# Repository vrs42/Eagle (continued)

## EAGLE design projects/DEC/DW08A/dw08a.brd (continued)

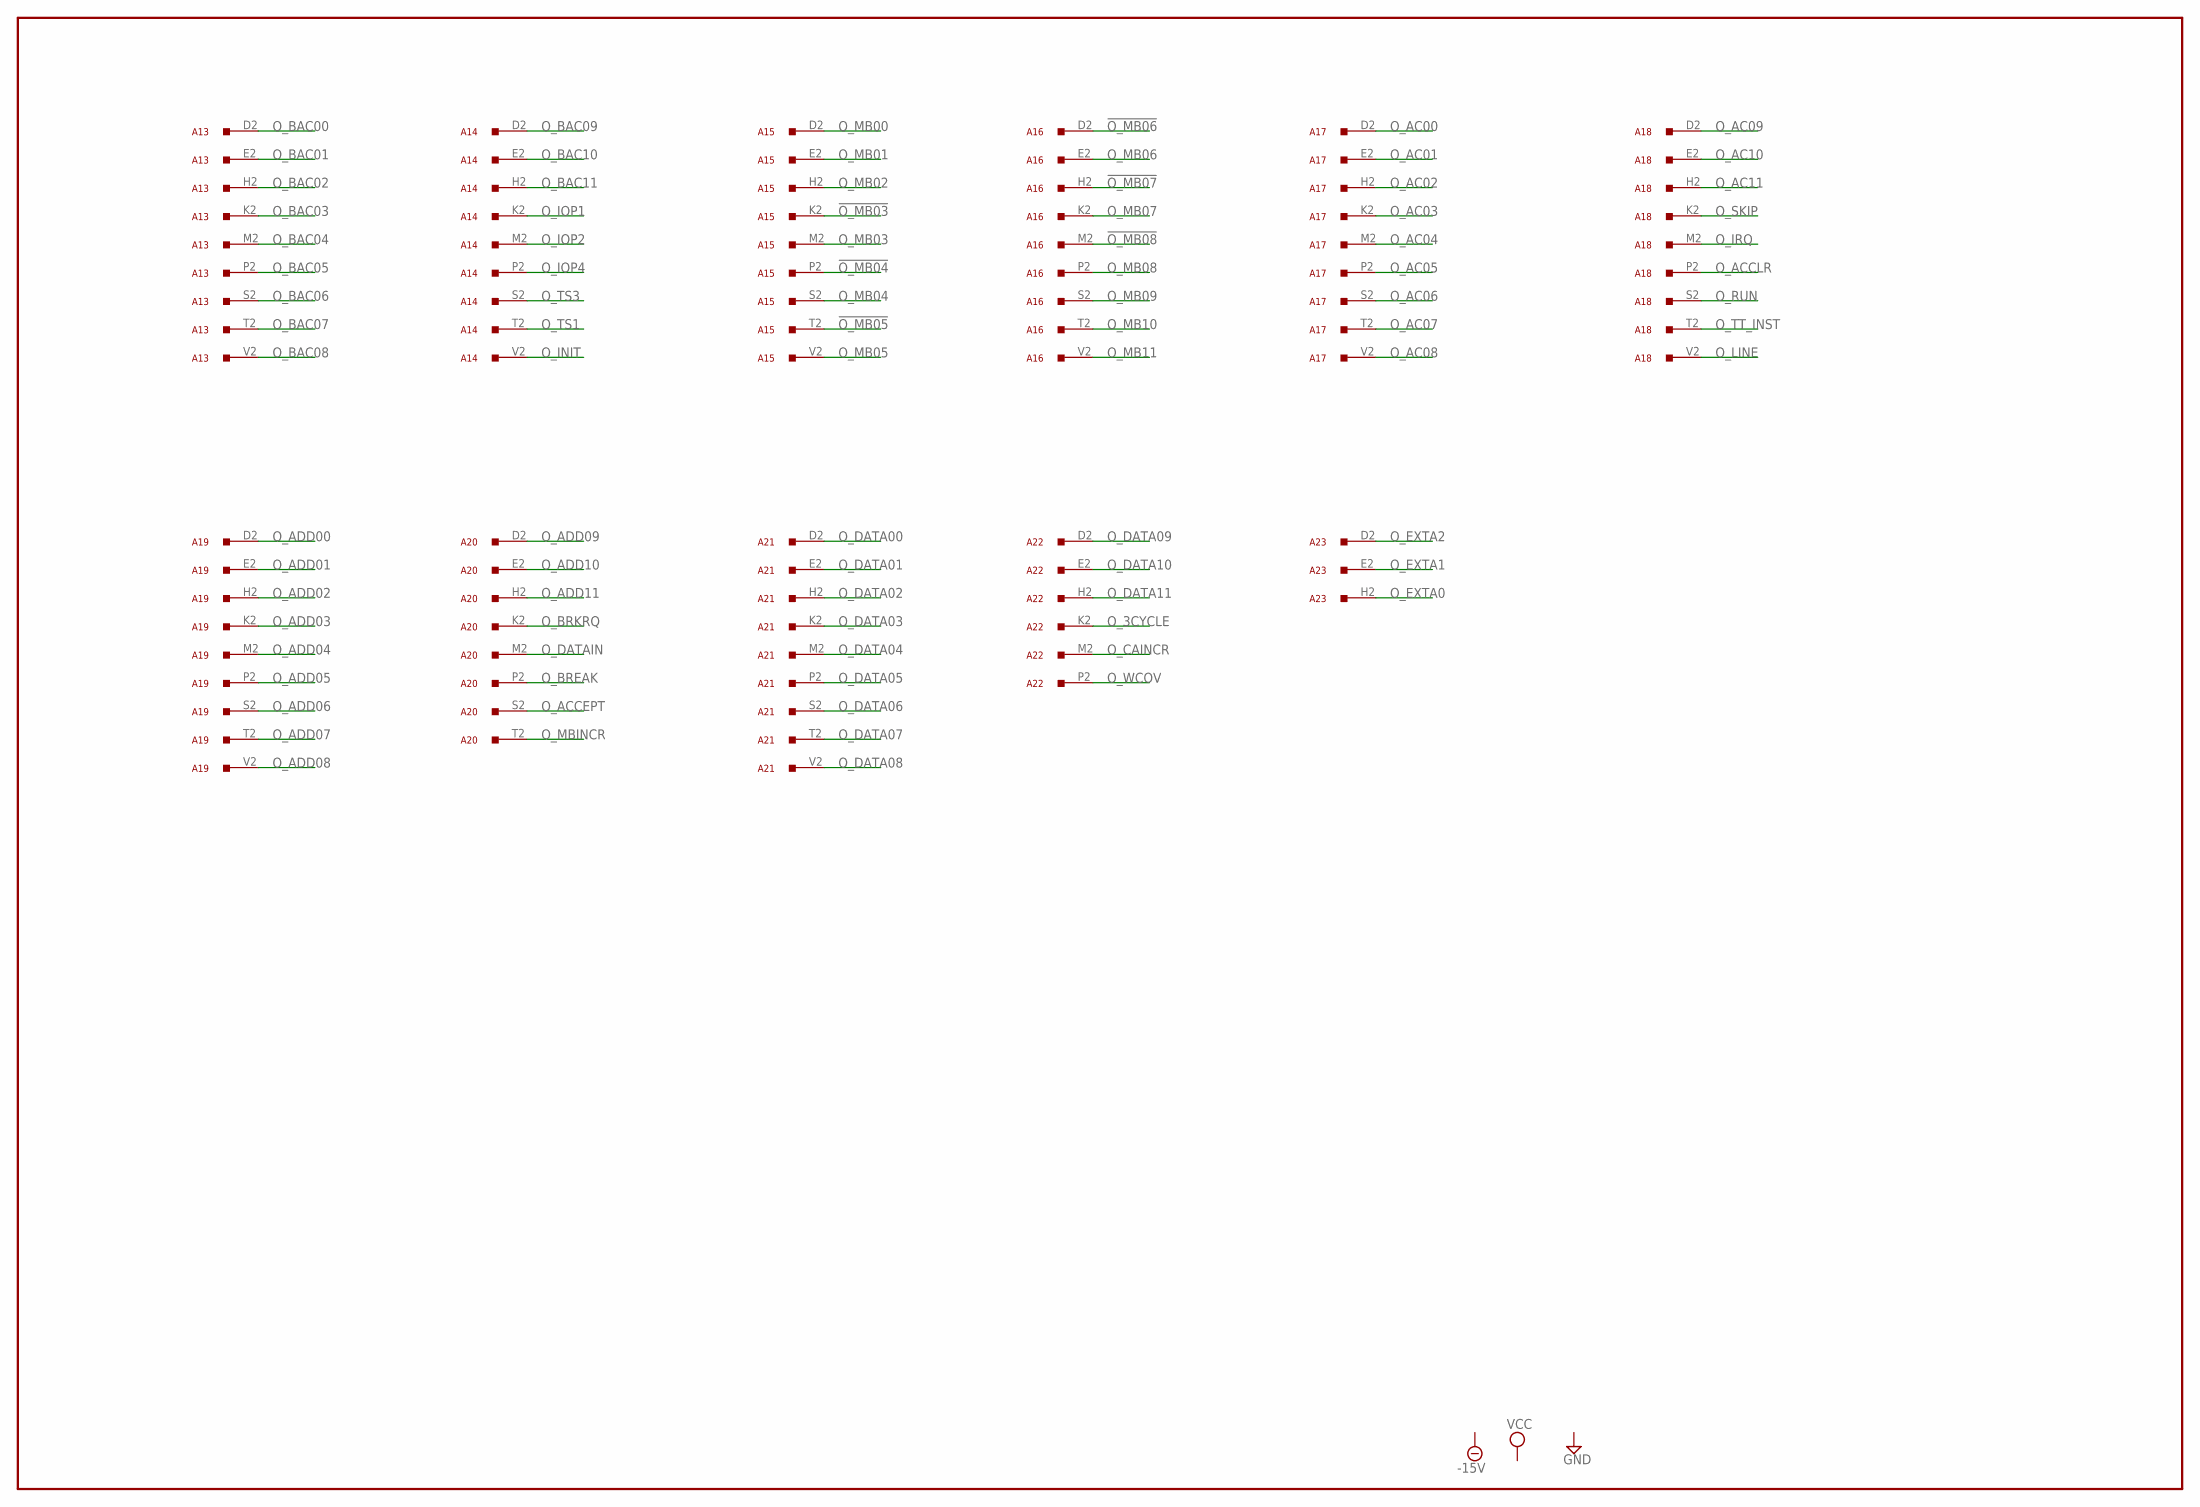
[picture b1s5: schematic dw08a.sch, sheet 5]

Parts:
A13, A14, A15, A16, A17, A18, A19, A20, A21, A22, A23: W011; H807

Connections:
!O_MB03: A15.K2; also elsewhere on the board
!O_MB04: A15.P2; also elsewhere on the board
!O_MB05: A15.T2; also elsewhere on the board
!O_MB06: A16.D2; also elsewhere on the board
!O_MB07: A16.H2; also elsewhere on the board
!O_MB08: A16.M2; also elsewhere on the board
GND: A13.C2 (GND), A13.F2 (GND), A13.J2 (GND), A13.L2 (GND), A13.N2 (GND), A13.R2 (GND), A13.U2 (GND), A14.C2 (GND), A14.F2 (GND), A14.J2 (GND), A14.L2 (GND), A14.N2 (GND), A14.R2 (GND), A14.U2 (GND), A15.C2 (GND), A15.F2 (GND), A15.J2 (GND), A15.L2 (GND), A15.N2 (GND), A15.R2 (GND), A15.U2 (GND), A16.C2 (GND), A16.F2 (GND), A16.J2 (GND), A16.L2 (GND), A16.N2 (GND), A16.R2 (GND), A16.U2 (GND), A17.C2 (GND), A17.F2 (GND), A17.J2 (GND), A17.L2 (GND), A17.N2 (GND), A17.R2 (GND), A17.U2 (GND), A18.C2 (GND), A18.F2 (GND), A18.J2 (GND), A18.L2 (GND), A18.N2 (GND), A18.R2 (GND), A18.U2 (GND), A19.C2 (GND), A19.F2 (GND), A19.J2 (GND), A19.L2 (GND), A19.N2 (GND), A19.R2 (GND), A19.U2 (GND), A20.C2 (GND), A20.F2 (GND), A20.J2 (GND), A20.L2 (GND), A20.N2 (GND), A20.R2 (GND), A20.U2 (GND), A21.C2 (GND), A21.F2 (GND), A21.J2 (GND), A21.L2 (GND), A21.N2 (GND), A21.R2 (GND), A21.U2 (GND), A22.C2 (GND), A22.F2 (GND), A22.J2 (GND), A22.L2 (GND), A22.N2 (GND), A22.R2 (GND), A22.U2 (GND), A23.C2 (GND), A23.F2 (GND), A23.J2 (GND), A23.L2 (GND), A23.N2 (GND), A23.R2 (GND), A23.U2 (GND); also elsewhere on the board
O_3CYCLE: A22.K2; also elsewhere on the board
O_AC00: A17.D2; also elsewhere on the board
O_AC01: A17.E2; also elsewhere on the board
O_AC02: A17.H2; also elsewhere on the board
O_AC03: A17.K2; also elsewhere on the board
O_AC04: A17.M2; also elsewhere on the board
O_AC05: A17.P2; also elsewhere on the board
O_AC06: A17.S2; also elsewhere on the board
O_AC07: A17.T2; also elsewhere on the board
O_AC08: A17.V2; also elsewhere on the board
O_AC09: A18.D2; also elsewhere on the board
O_AC10: A18.E2; also elsewhere on the board
O_AC11: A18.H2; also elsewhere on the board
O_ACCEPT: A20.S2; also elsewhere on the board
O_ACCLR: A18.P2; also elsewhere on the board
O_ADD00: A19.D2; also elsewhere on the board
O_ADD01: A19.E2; also elsewhere on the board
O_ADD02: A19.H2; also elsewhere on the board
O_ADD03: A19.K2; also elsewhere on the board
O_ADD04: A19.M2; also elsewhere on the board
O_ADD05: A19.P2; also elsewhere on the board
O_ADD06: A19.S2; also elsewhere on the board
O_ADD07: A19.T2; also elsewhere on the board
O_ADD08: A19.V2; also elsewhere on the board
O_ADD09: A20.D2; also elsewhere on the board
O_ADD10: A20.E2; also elsewhere on the board
O_ADD11: A20.H2; also elsewhere on the board
O_BAC00: A13.D2; also elsewhere on the board
O_BAC01: A13.E2; also elsewhere on the board
O_BAC02: A13.H2; also elsewhere on the board
O_BAC03: A13.K2; also elsewhere on the board
O_BAC04: A13.M2; also elsewhere on the board
O_BAC05: A13.P2; also elsewhere on the board
O_BAC06: A13.S2; also elsewhere on the board
O_BAC07: A13.T2; also elsewhere on the board
O_BAC08: A13.V2; also elsewhere on the board
O_BAC09: A14.D2; also elsewhere on the board
O_BAC10: A14.E2; also elsewhere on the board
O_BAC11: A14.H2; also elsewhere on the board
O_BREAK: A20.P2; also elsewhere on the board
O_BRKRQ: A20.K2; also elsewhere on the board
O_CAINCR: A22.M2; also elsewhere on the board
O_DATA00: A21.D2; also elsewhere on the board
O_DATA01: A21.E2; also elsewhere on the board
O_DATA02: A21.H2; also elsewhere on the board
O_DATA03: A21.K2; also elsewhere on the board
O_DATA04: A21.M2; also elsewhere on the board
O_DATA05: A21.P2; also elsewhere on the board
O_DATA06: A21.S2; also elsewhere on the board
O_DATA07: A21.T2; also elsewhere on the board
O_DATA08: A21.V2; also elsewhere on the board
O_DATA09: A22.D2; also elsewhere on the board
O_DATA10: A22.E2; also elsewhere on the board
O_DATA11: A22.H2; also elsewhere on the board
O_DATAIN: A20.M2; also elsewhere on the board
O_EXTA0: A23.H2; also elsewhere on the board
O_EXTA1: A23.E2; also elsewhere on the board
O_EXTA2: A23.D2; also elsewhere on the board
O_INIT: A14.V2; also elsewhere on the board
O_IOP1: A14.K2; also elsewhere on the board
O_IOP2: A14.M2; also elsewhere on the board
O_IOP4: A14.P2; also elsewhere on the board
O_IRQ: A18.M2; also elsewhere on the board
O_LINE: A18.V2; also elsewhere on the board
O_MB00: A15.D2; also elsewhere on the board
O_MB01: A15.E2; also elsewhere on the board
O_MB02: A15.H2; also elsewhere on the board
O_MB03: A15.M2; also elsewhere on the board
O_MB04: A15.S2; also elsewhere on the board
O_MB05: A15.V2; also elsewhere on the board
O_MB06: A16.E2; also elsewhere on the board
O_MB07: A16.K2; also elsewhere on the board
O_MB08: A16.P2; also elsewhere on the board
O_MB09: A16.S2; also elsewhere on the board
O_MB10: A16.T2; also elsewhere on the board
O_MB11: A16.V2; also elsewhere on the board
O_MBINCR: A20.T2; also elsewhere on the board
O_RUN: A18.S2; also elsewhere on the board
O_SKIP: A18.K2; also elsewhere on the board
O_TS1: A14.T2; also elsewhere on the board
O_TS3: A14.S2; also elsewhere on the board
O_TT_INST: A18.T2; also elsewhere on the board
O_WCOV: A22.P2; also elsewhere on the board

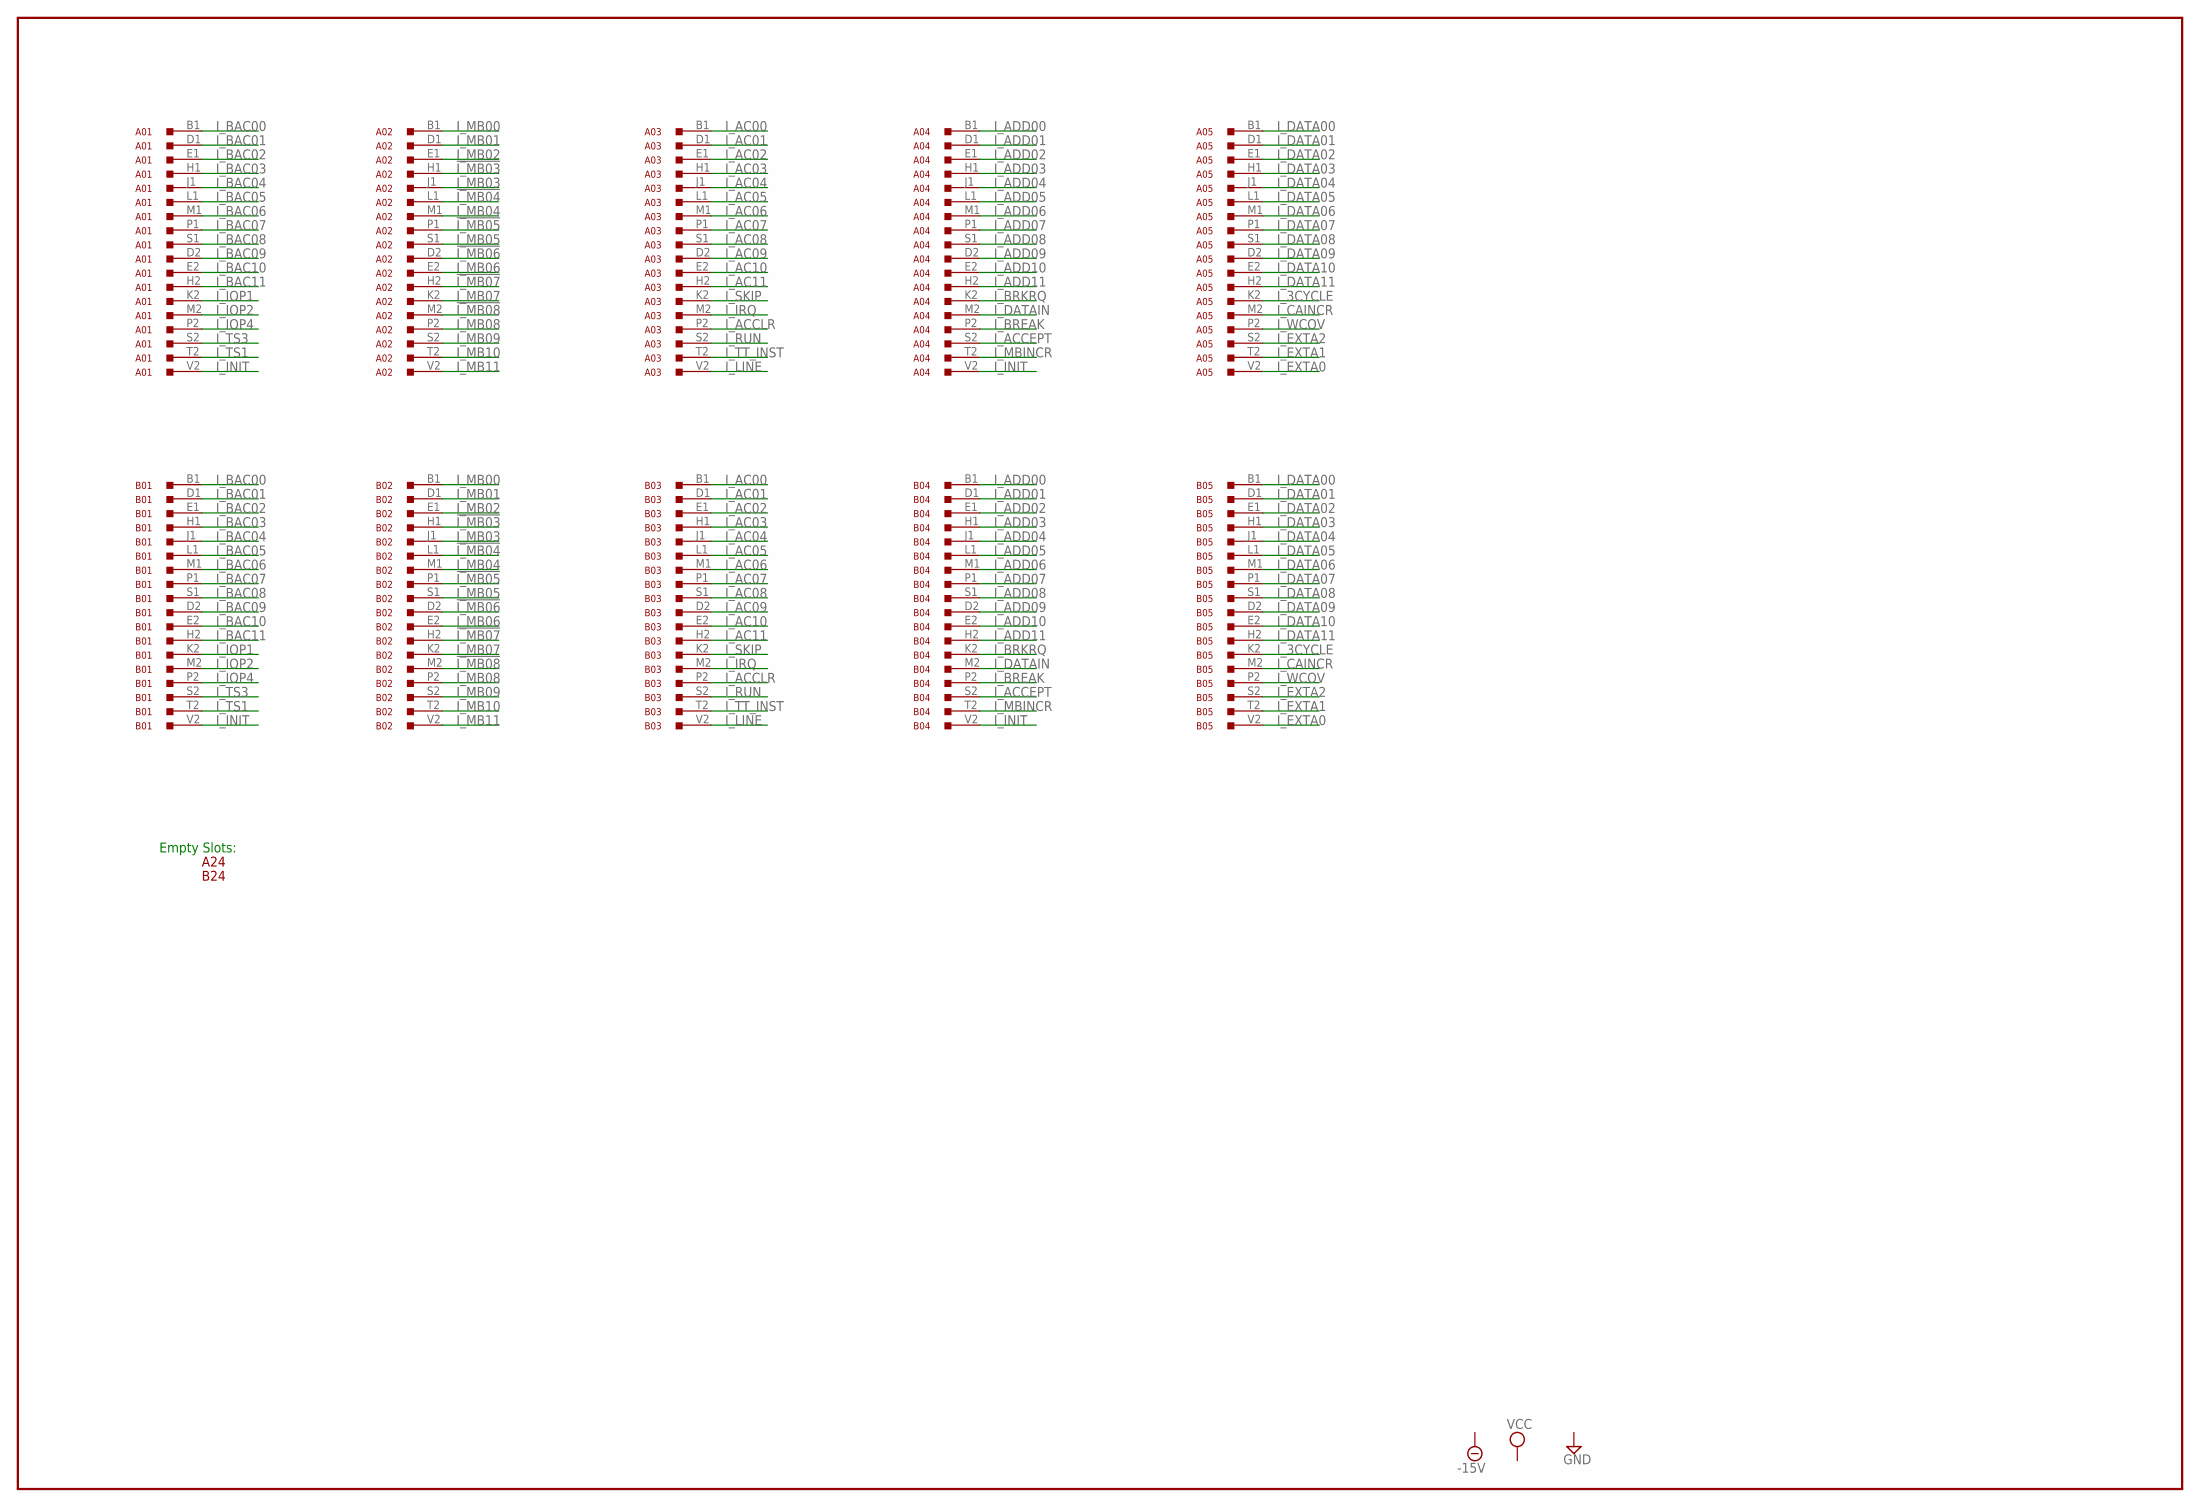
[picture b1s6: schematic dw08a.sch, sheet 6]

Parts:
A01, A02, A03, A04, A05: M903; H807
A24: H807
B01, B02, B03, B04, B05: M903; H807
B24: H807

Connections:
!I_MB03: A02.H1, B02.H1; also elsewhere on the board
!I_MB04: A02.L1, B02.L1; also elsewhere on the board
!I_MB05: A02.P1, B02.P1; also elsewhere on the board
!I_MB06: A02.D2, B02.D2; also elsewhere on the board
!I_MB07: A02.H2, B02.H2; also elsewhere on the board
!I_MB08: A02.M2, B02.M2; also elsewhere on the board
GND: A01.A1 (GND), A01.C1 (GND), A01.C2 (GND), A01.F1 (GND), A01.F2 (GND), A01.J2 (GND), A01.K1 (GND), A01.L2 (GND), A01.N1 (GND), A01.N2 (GND), A01.R1 (GND), A01.R2 (GND), A01.T1 (GND), A01.U2 (GND), A02.A1 (GND), A02.C1 (GND), A02.C2 (GND), A02.F1 (GND), A02.F2 (GND), A02.J2 (GND), A02.K1 (GND), A02.L2 (GND), A02.N1 (GND), A02.N2 (GND), A02.R1 (GND), A02.R2 (GND), A02.T1 (GND), A02.U2 (GND), A03.A1 (GND), A03.C1 (GND), A03.C2 (GND), A03.F1 (GND), A03.F2 (GND), A03.J2 (GND), A03.K1 (GND), A03.L2 (GND), A03.N1 (GND), A03.N2 (GND), A03.R1 (GND), A03.R2 (GND), A03.T1 (GND), A03.U2 (GND), A04.A1 (GND), A04.C1 (GND), A04.C2 (GND), A04.F1 (GND), A04.F2 (GND), A04.J2 (GND), A04.K1 (GND), A04.L2 (GND), A04.N1 (GND), A04.N2 (GND), A04.R1 (GND), A04.R2 (GND), A04.T1 (GND), A04.U2 (GND), A05.A1 (GND), A05.C1 (GND), A05.C2 (GND), A05.F1 (GND), A05.F2 (GND), A05.J2 (GND), A05.K1 (GND), A05.L2 (GND), A05.N1 (GND), A05.N2 (GND), A05.R1 (GND), A05.R2 (GND), A05.T1 (GND), A05.U2 (GND), B01.A1 (GND), B01.C1 (GND), B01.C2 (GND), B01.F1 (GND), B01.F2 (GND), B01.J2 (GND), B01.K1 (GND), B01.L2 (GND), B01.N1 (GND), B01.N2 (GND), B01.R1 (GND), B01.R2 (GND), B01.T1 (GND), B01.U2 (GND), B02.A1 (GND), B02.C1 (GND), B02.C2 (GND), B02.F1 (GND), B02.F2 (GND), B02.J2 (GND), B02.K1 (GND), B02.L2 (GND), B02.N1 (GND), B02.N2 (GND), B02.R1 (GND), B02.R2 (GND), B02.T1 (GND), B02.U2 (GND), B03.A1 (GND), B03.C1 (GND), B03.C2 (GND), B03.F1 (GND), B03.F2 (GND), B03.J2 (GND), B03.K1 (GND), B03.L2 (GND), B03.N1 (GND), B03.N2 (GND), B03.R1 (GND), B03.R2 (GND), B03.T1 (GND), B03.U2 (GND), B04.A1 (GND), B04.C1 (GND), B04.C2 (GND), B04.F1 (GND), B04.F2 (GND), B04.J2 (GND), B04.K1 (GND), B04.L2 (GND), B04.N1 (GND), B04.N2 (GND), B04.R1 (GND), B04.R2 (GND), B04.T1 (GND), B04.U2 (GND), B05.A1 (GND), B05.C1 (GND), B05.C2 (GND), B05.F1 (GND), B05.F2 (GND), B05.J2 (GND), B05.K1 (GND), B05.L2 (GND), B05.N1 (GND), B05.N2 (GND), B05.R1 (GND), B05.R2 (GND), B05.T1 (GND), B05.U2 (GND); also elsewhere on the board
I_3CYCLE: A05.K2, B05.K2; also elsewhere on the board
I_AC00: A03.B1, B03.B1; also elsewhere on the board
I_AC01: A03.D1, B03.D1; also elsewhere on the board
I_AC02: A03.E1, B03.E1; also elsewhere on the board
I_AC03: A03.H1, B03.H1; also elsewhere on the board
I_AC04: A03.J1, B03.J1; also elsewhere on the board
I_AC05: A03.L1, B03.L1; also elsewhere on the board
I_AC06: A03.M1, B03.M1; also elsewhere on the board
I_AC07: A03.P1, B03.P1; also elsewhere on the board
I_AC08: A03.S1, B03.S1; also elsewhere on the board
I_AC09: A03.D2, B03.D2; also elsewhere on the board
I_AC10: A03.E2, B03.E2; also elsewhere on the board
I_AC11: A03.H2, B03.H2; also elsewhere on the board
I_ACCEPT: A04.S2, B04.S2; also elsewhere on the board
I_ACCLR: A03.P2, B03.P2; also elsewhere on the board
I_ADD00: A04.B1, B04.B1; also elsewhere on the board
I_ADD01: A04.D1, B04.D1; also elsewhere on the board
I_ADD02: A04.E1, B04.E1; also elsewhere on the board
I_ADD03: A04.H1, B04.H1; also elsewhere on the board
I_ADD04: A04.J1, B04.J1; also elsewhere on the board
I_ADD05: A04.L1, B04.L1; also elsewhere on the board
I_ADD06: A04.M1, B04.M1; also elsewhere on the board
I_ADD07: A04.P1, B04.P1; also elsewhere on the board
I_ADD08: A04.S1, B04.S1; also elsewhere on the board
I_ADD09: A04.D2, B04.D2; also elsewhere on the board
I_ADD10: A04.E2, B04.E2; also elsewhere on the board
I_ADD11: A04.H2, B04.H2; also elsewhere on the board
I_BAC00: A01.B1, B01.B1; also elsewhere on the board
I_BAC01: A01.D1, B01.D1; also elsewhere on the board
I_BAC02: A01.E1, B01.E1; also elsewhere on the board
I_BAC03: A01.H1, B01.H1; also elsewhere on the board
I_BAC04: A01.J1, B01.J1; also elsewhere on the board
I_BAC05: A01.L1, B01.L1; also elsewhere on the board
I_BAC06: A01.M1, B01.M1; also elsewhere on the board
I_BAC07: A01.P1, B01.P1; also elsewhere on the board
I_BAC08: A01.S1, B01.S1; also elsewhere on the board
I_BAC09: A01.D2, B01.D2; also elsewhere on the board
I_BAC10: A01.E2, B01.E2; also elsewhere on the board
I_BAC11: A01.H2, B01.H2; also elsewhere on the board
I_BREAK: A04.P2, B04.P2; also elsewhere on the board
I_BRKRQ: A04.K2, B04.K2; also elsewhere on the board
I_CAINCR: A05.M2, B05.M2; also elsewhere on the board
I_DATA00: A05.B1, B05.B1; also elsewhere on the board
I_DATA01: A05.D1, B05.D1; also elsewhere on the board
I_DATA02: A05.E1, B05.E1; also elsewhere on the board
I_DATA03: A05.H1, B05.H1; also elsewhere on the board
I_DATA04: A05.J1, B05.J1; also elsewhere on the board
I_DATA05: A05.L1, B05.L1; also elsewhere on the board
I_DATA06: A05.M1, B05.M1; also elsewhere on the board
I_DATA07: A05.P1, B05.P1; also elsewhere on the board
I_DATA08: A05.S1, B05.S1; also elsewhere on the board
I_DATA09: A05.D2, B05.D2; also elsewhere on the board
I_DATA10: A05.E2, B05.E2; also elsewhere on the board
I_DATA11: A05.H2, B05.H2; also elsewhere on the board
I_DATAIN: A04.M2, B04.M2; also elsewhere on the board
I_EXTA0: A05.V2, B05.V2; also elsewhere on the board
I_EXTA1: A05.T2, B05.T2; also elsewhere on the board
I_EXTA2: A05.S2, B05.S2; also elsewhere on the board
I_INIT: A01.V2, A04.V2, B01.V2, B04.V2; also elsewhere on the board
I_IOP1: A01.K2, B01.K2; also elsewhere on the board
I_IOP2: A01.M2, B01.M2; also elsewhere on the board
I_IOP4: A01.P2, B01.P2; also elsewhere on the board
I_IRQ: A03.M2, B03.M2; also elsewhere on the board
I_LINE: A03.V2, B03.V2; also elsewhere on the board
I_MB00: A02.B1, B02.B1; also elsewhere on the board
I_MB01: A02.D1, B02.D1; also elsewhere on the board
I_MB02: A02.E1, B02.E1; also elsewhere on the board
I_MB03: A02.J1, B02.J1; also elsewhere on the board
I_MB04: A02.M1, B02.M1; also elsewhere on the board
I_MB05: A02.S1, B02.S1; also elsewhere on the board
I_MB06: A02.E2, B02.E2; also elsewhere on the board
I_MB07: A02.K2, B02.K2; also elsewhere on the board
I_MB08: A02.P2, B02.P2; also elsewhere on the board
I_MB09: A02.S2, B02.S2; also elsewhere on the board
I_MB10: A02.T2, B02.T2; also elsewhere on the board
I_MB11: A02.V2, B02.V2; also elsewhere on the board
I_MBINCR: A04.T2, B04.T2; also elsewhere on the board
I_RUN: A03.S2, B03.S2; also elsewhere on the board
I_SKIP: A03.K2, B03.K2; also elsewhere on the board
I_TS1: A01.T2, B01.T2; also elsewhere on the board
I_TS3: A01.S2, B01.S2; also elsewhere on the board
I_TT_INST: A03.T2, B03.T2; also elsewhere on the board
I_WCOV: A05.P2, B05.P2; also elsewhere on the board

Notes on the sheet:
Empty Slots:

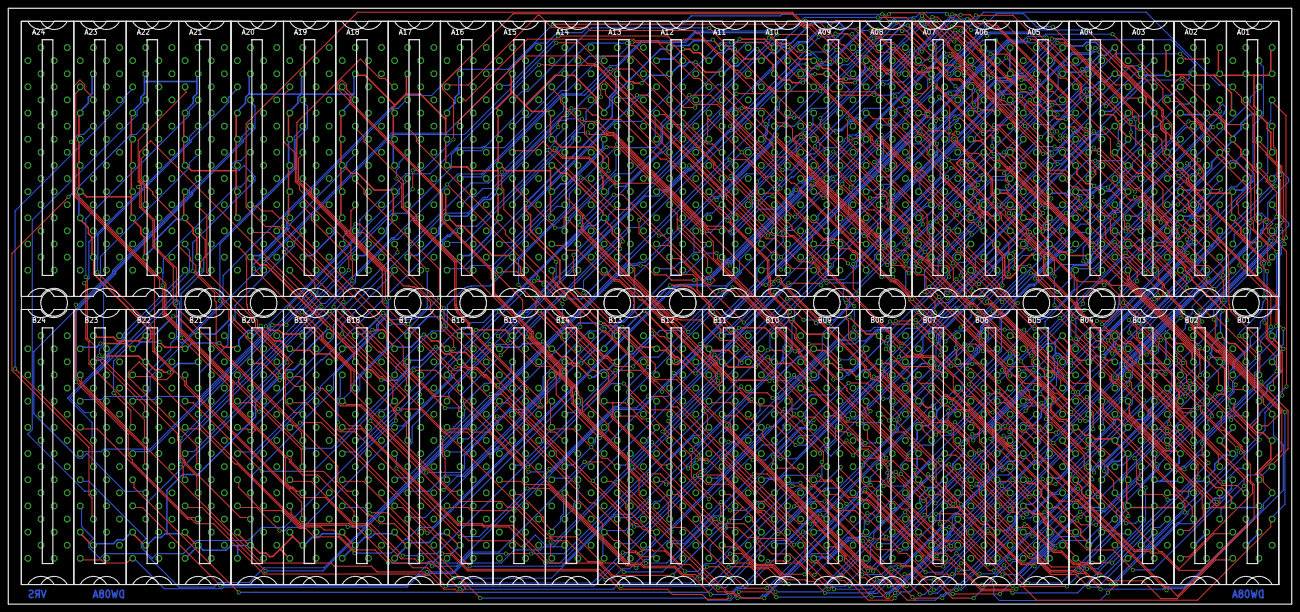
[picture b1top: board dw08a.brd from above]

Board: 2 copper layers, 311.1 x 144.5 mm, 54 parts (0 on the bottom side), 191 nets.

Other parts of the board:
U$1, U$2, U$3, U$4, U$5, U$6: CBLOCK

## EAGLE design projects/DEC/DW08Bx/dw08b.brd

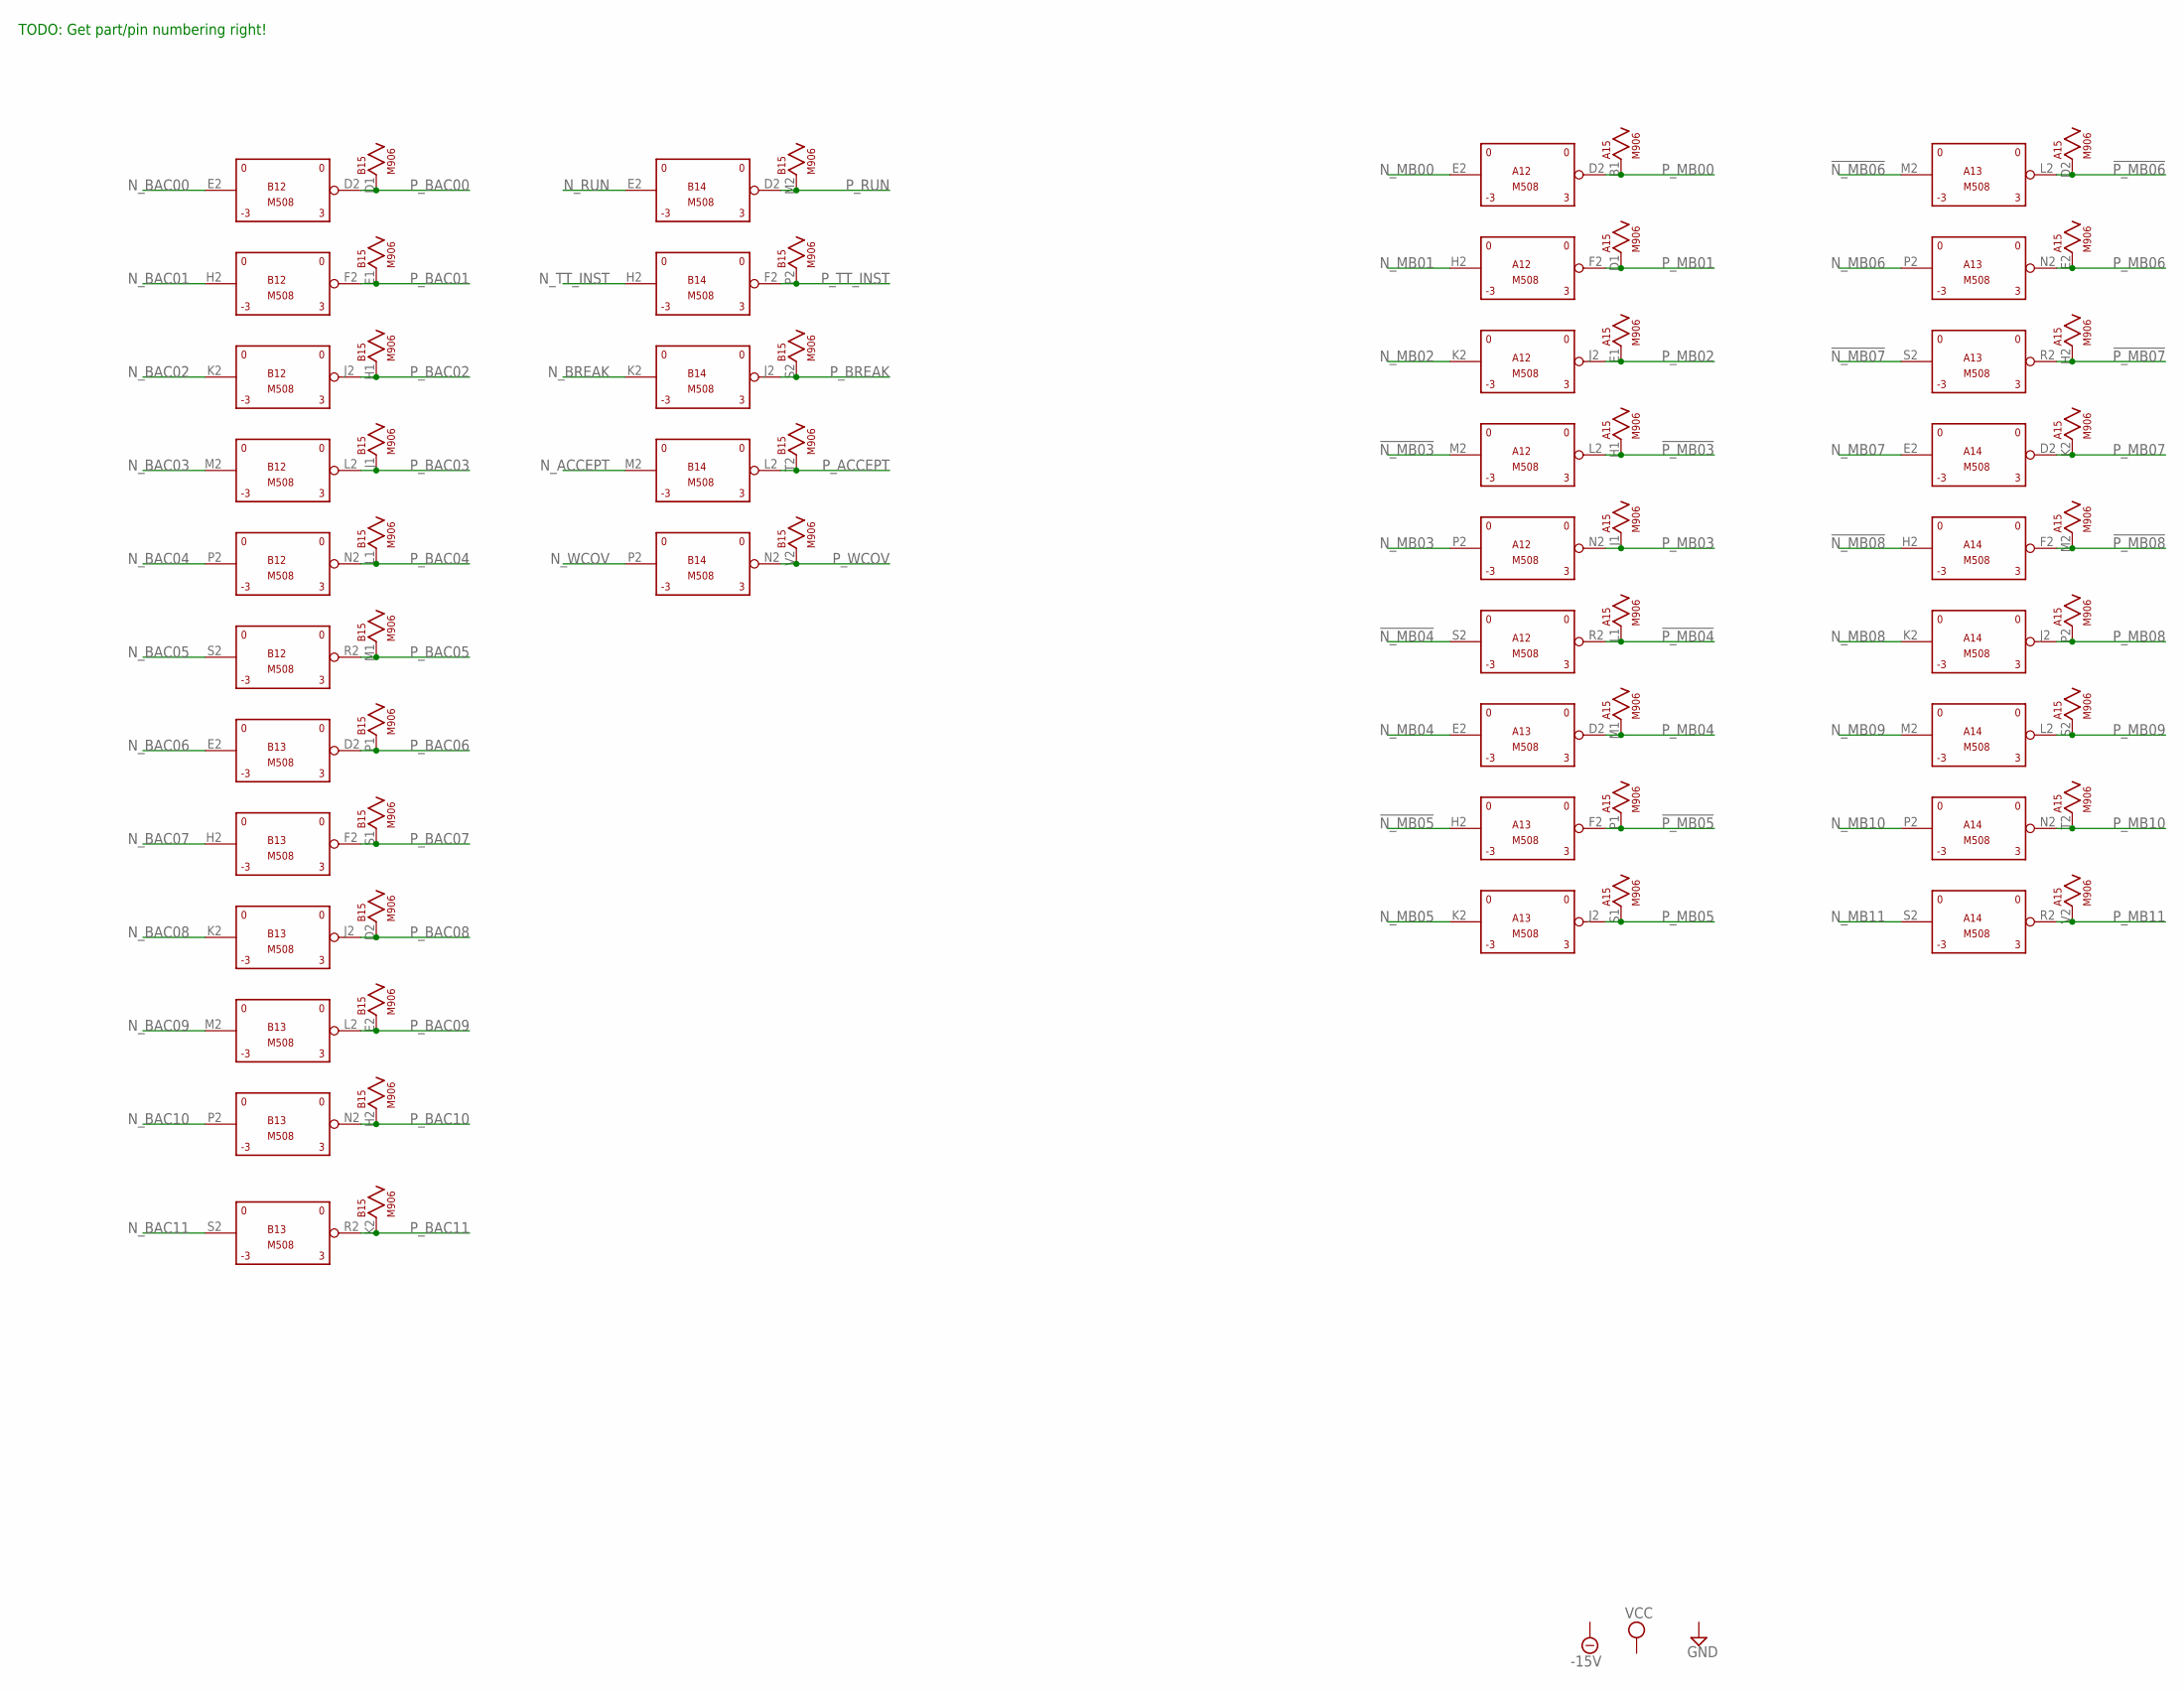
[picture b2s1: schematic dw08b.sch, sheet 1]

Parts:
A12, A13, A14: M508; H807
A15: M906; H807
B12, B13, B14: M508; H807
B15: M906; H807

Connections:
!N_MB03: A12.M2 (IN); also elsewhere on the board
!N_MB04: A12.S2 (IN); also elsewhere on the board
!N_MB05: A13.H2 (IN); also elsewhere on the board
!N_MB06: A13.M2 (IN); also elsewhere on the board
!N_MB07: A13.S2 (IN); also elsewhere on the board
!N_MB08: A14.H2 (IN); also elsewhere on the board
!P_MB03: A12.L2 (OUT), A15.H1; also elsewhere on the board
!P_MB04: A12.R2 (OUT), A15.L1; also elsewhere on the board
!P_MB05: A13.F2 (OUT), A15.P1; also elsewhere on the board
!P_MB06: A13.L2 (OUT), A15.D2; also elsewhere on the board
!P_MB07: A13.R2 (OUT), A15.H2; also elsewhere on the board
!P_MB08: A14.F2 (OUT), A15.M2; also elsewhere on the board
-15V: A12.B2 (-15V), A13.B2 (-15V), A14.B2 (-15V), B12.B2 (-15V), B13.B2 (-15V), B14.B2 (-15V); also elsewhere on the board
GND: A12.C2 (GND), A13.C2 (GND), A14.C2 (GND), A15.A1 (GND), A15.C1 (GND), A15.C2 (GND), A15.F1 (GND), A15.F2 (GND), A15.J2 (GND), A15.K1 (GND), A15.L2 (GND), A15.N1 (GND), A15.N2 (GND), A15.R1 (GND), A15.R2 (GND), A15.T1 (GND), A15.U2 (GND), B12.C2 (GND), B13.C2 (GND), B14.C2 (GND), B15.A1 (GND), B15.C1 (GND), B15.C2 (GND), B15.F1 (GND), B15.F2 (GND), B15.J2 (GND), B15.K1 (GND), B15.L2 (GND), B15.N1 (GND), B15.N2 (GND), B15.R1 (GND), B15.R2 (GND), B15.T1 (GND), B15.U2 (GND); also elsewhere on the board
N_ACCEPT: B14.M2 (IN); also elsewhere on the board
N_BAC00: B12.E2 (IN); also elsewhere on the board
N_BAC01: B12.H2 (IN); also elsewhere on the board
N_BAC02: B12.K2 (IN); also elsewhere on the board
N_BAC03: B12.M2 (IN); also elsewhere on the board
N_BAC04: B12.P2 (IN); also elsewhere on the board
N_BAC05: B12.S2 (IN); also elsewhere on the board
N_BAC06: B13.E2 (IN); also elsewhere on the board
N_BAC07: B13.H2 (IN); also elsewhere on the board
N_BAC08: B13.K2 (IN); also elsewhere on the board
N_BAC09: B13.M2 (IN); also elsewhere on the board
N_BAC10: B13.P2 (IN); also elsewhere on the board
N_BAC11: B13.S2 (IN); also elsewhere on the board
N_BREAK: B14.K2 (IN); also elsewhere on the board
N_MB00: A12.E2 (IN); also elsewhere on the board
N_MB01: A12.H2 (IN); also elsewhere on the board
N_MB02: A12.K2 (IN); also elsewhere on the board
N_MB03: A12.P2 (IN); also elsewhere on the board
N_MB04: A13.E2 (IN); also elsewhere on the board
N_MB05: A13.K2 (IN); also elsewhere on the board
N_MB06: A13.P2 (IN); also elsewhere on the board
N_MB07: A14.E2 (IN); also elsewhere on the board
N_MB08: A14.K2 (IN); also elsewhere on the board
N_MB09: A14.M2 (IN); also elsewhere on the board
N_MB10: A14.P2 (IN); also elsewhere on the board
N_MB11: A14.S2 (IN); also elsewhere on the board
N_RUN: B14.E2 (IN); also elsewhere on the board
N_TT_INST: B14.H2 (IN); also elsewhere on the board
N_WCOV: B14.P2 (IN); also elsewhere on the board
P_ACCEPT: B14.L2 (OUT), B15.T2; also elsewhere on the board
P_BAC00: B12.D2 (OUT), B15.D1; also elsewhere on the board
P_BAC01: B12.F2 (OUT), B15.E1; also elsewhere on the board
P_BAC02: B12.J2 (OUT), B15.H1; also elsewhere on the board
P_BAC03: B12.L2 (OUT), B15.J1; also elsewhere on the board
P_BAC04: B12.N2 (OUT), B15.L1; also elsewhere on the board
P_BAC05: B12.R2 (OUT), B15.M1; also elsewhere on the board
P_BAC06: B13.D2 (OUT), B15.P1; also elsewhere on the board
P_BAC07: B13.F2 (OUT), B15.S1; also elsewhere on the board
P_BAC08: B13.J2 (OUT), B15.D2; also elsewhere on the board
P_BAC09: B13.L2 (OUT), B15.E2; also elsewhere on the board
P_BAC10: B13.N2 (OUT), B15.H2; also elsewhere on the board
P_BAC11: B13.R2 (OUT), B15.K2; also elsewhere on the board
P_BREAK: B14.J2 (OUT), B15.S2; also elsewhere on the board
P_MB00: A12.D2 (OUT), A15.B1; also elsewhere on the board
P_MB01: A12.F2 (OUT), A15.D1; also elsewhere on the board
P_MB02: A12.J2 (OUT), A15.E1; also elsewhere on the board
P_MB03: A12.N2 (OUT), A15.J1; also elsewhere on the board
P_MB04: A13.D2 (OUT), A15.M1; also elsewhere on the board
P_MB05: A13.J2 (OUT), A15.S1; also elsewhere on the board
P_MB06: A13.N2 (OUT), A15.E2; also elsewhere on the board
P_MB07: A14.D2 (OUT), A15.K2; also elsewhere on the board
P_MB08: A14.J2 (OUT), A15.P2; also elsewhere on the board
P_MB09: A14.L2 (OUT), A15.S2; also elsewhere on the board
P_MB10: A14.N2 (OUT), A15.T2; also elsewhere on the board
P_MB11: A14.R2 (OUT), A15.V2; also elsewhere on the board
P_RUN: B14.D2 (OUT), B15.M2; also elsewhere on the board
P_TT_INST: B14.F2 (OUT), B15.P2; also elsewhere on the board
P_WCOV: B14.N2 (OUT), B15.V2; also elsewhere on the board
VCC: A12.A2 (VCC), A13.A2 (VCC), A14.A2 (VCC), A15.A2 (VCC), B12.A2 (VCC), B13.A2 (VCC), B14.A2 (VCC), B15.A2 (VCC); also elsewhere on the board

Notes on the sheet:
TODO: Get part/pin numbering right!
